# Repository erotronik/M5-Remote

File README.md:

# M5 REMOTE

Please note that this is a modification of the OSSM-M5-Remote project by Ortlof, which is available at [https://github.com/ortlof/OSSM-M5-Remote](https://github.com/ortlof/OSSM-M5-Remote).

Also note that this is an early prototype that is not tested.

This modified project adds RGB Rotary encoders that can light the knobs, and allows the installation of an LED in the push-button.

Furthermore, communication with the board is switched to I2C, using a PWM controller for the LEDs and a port expander for the Rotary encoders. Note that this means that this modification is *not compatible* with the software written for the original OSSM M5 Remote. Currently, there only is a skeleton project [that sketches how to interface with the components on the board in the Firmware folder](./Firmware).

The modified PCB design can be found in the `Hardware/PCB` folder.

The remaining folders in this project are unchanged - please note that the software contained in this repository will not work with the changed hardware.

## Overview of the M5-Remote

The M5 Remote is a remote control platform, e.g. for Sex Toys, or estim devices.

The original project was developed for the OSSM project (https://github.com/KinkyMakers/OSSM-hardware).

This modified version currently does not have direct support for any toys, and requires you to write your own software.

To help with development and design join the KinkyMakers Discord: https://discord.gg/MmpT9xE . Be sure to say hello in the #m5-remote channel. 

# Build the M5 Remote Yourself

## PCB from JLCPCB

The PCB is designed to be made using the JLCPCB assembly service.

To order the PCB, go to [JLCPCP](https://jlcpcb.com) and upload the gerber zip contained in `PCB/jlcpcb`. Leave all settings at default - you can change the PCB colour if you want.

Enable "PCB" assembly, and choose "assemble bottom side" (not selected by default).

In the next step, upload `bom.csv` and `positions.csv`. Verify that the positioning of the components looks corerct before ordering.

## Bill Of Materials for sourcing Electrical Components

BOM is on Octopart for Easy Sourcing: https://octopart.com/bom-tool/pqx0O8QI

## Additional parts needed that are not found on Octopart:

Note - instead of the Kailh switches from pimoroni, any Cherry-compatible switch with LED hole can be used.

| Quantity | Part | Sourcing EU | Price € |
|----------|------|-------------|---------|
| 1x | Switch | https://shop.pimoroni.com/products/kailh-mechanical-switches-pack-of-12?variant=32056315314259 | 7
| 2x | M3x25mm Hex Head Cap Bolt | https://www.amazon.de/Edelstahl-Innensechskant-Bolzenset-Eisenrahmen-Mechanischer-Innensechskantschraube-Mutternset/dp/B07PPFT871/ | 12,97 € |
| 4x | M3x20mm Hex Head Cap Bolt | Comes as part of the set mentioned above | " | 
| 4x | Heat Set inserts M3 | https://www.amazon.de/ruthex-Gewindeeinsatz-St%C3%BCck-Gewindebuchsen-Kunststoffteile/dp/B08BCRZZS3 | 8,99 € |
| 1x | 3,7v 2000mAh Lipo Batterie Size 34,5 mm x 10,6 mm x 56 mm | https://www.amazon.de/EEMB-103454-2AhLithium-Schutzplatine-Isolationsbeschichtung/dp/B08214DJLJ/ | 14,89 € |

--------------------------------------------

| Quantity | Part | Sourcing US | Price $ |
|----------|------|-------------|---------|
| 2x | M3x25mm Hex Head Cap Bolt | https://www.amazon.com/dp/B09NR8X2LV | $17.99 |
| 4x | M3x20mm Hex Head Cap Bolt | Comes as part of the set mentioned above | " | 
| 4x | Heat Set inserts M3 | https://www.amazon.com/ruthex-M3-Threaded-Inserts-RX-M3x5-7/dp/B08BCRZZS3 | $10.99 |
| 1x | 3.7v 2000mAh Lipo Battery Size 34.5 X 56 X 10.6 mm (The wires will need to be reversed in the connector on this one! See Assembly instructions for more info.) | https://www.amazon.com/EEMB-2000mAh-Battery-Rechargeable-Connector/dp/B08214DJLJ/ | $14.99 |

## 3D Printed Parts Needed:

| Quantity | Part | Information |
|----------|------|-------------|
| 1x | Bottom.stl or Bottom_Adafruit_LIPO.stl or Bottom-Magnets.stl| There is a specific version for the wider Adafruit LIPO battery. Print with the base side facing down, 6 walls 20% Infill | 
| 1x | TOP-*-Keycap-Standoff.stl | Top Depends on your Keycap: Cherry or DSA (DSA is wider) | 
| 4x | M5_Remote_Knob_Customizable.scad | If you go for the 3d Printed knobs |

Filament - A good quality PLA works well. While there are no threads it is recommended that your printer is well calibrated.  

# [Assembly instructions](Assembly.md)

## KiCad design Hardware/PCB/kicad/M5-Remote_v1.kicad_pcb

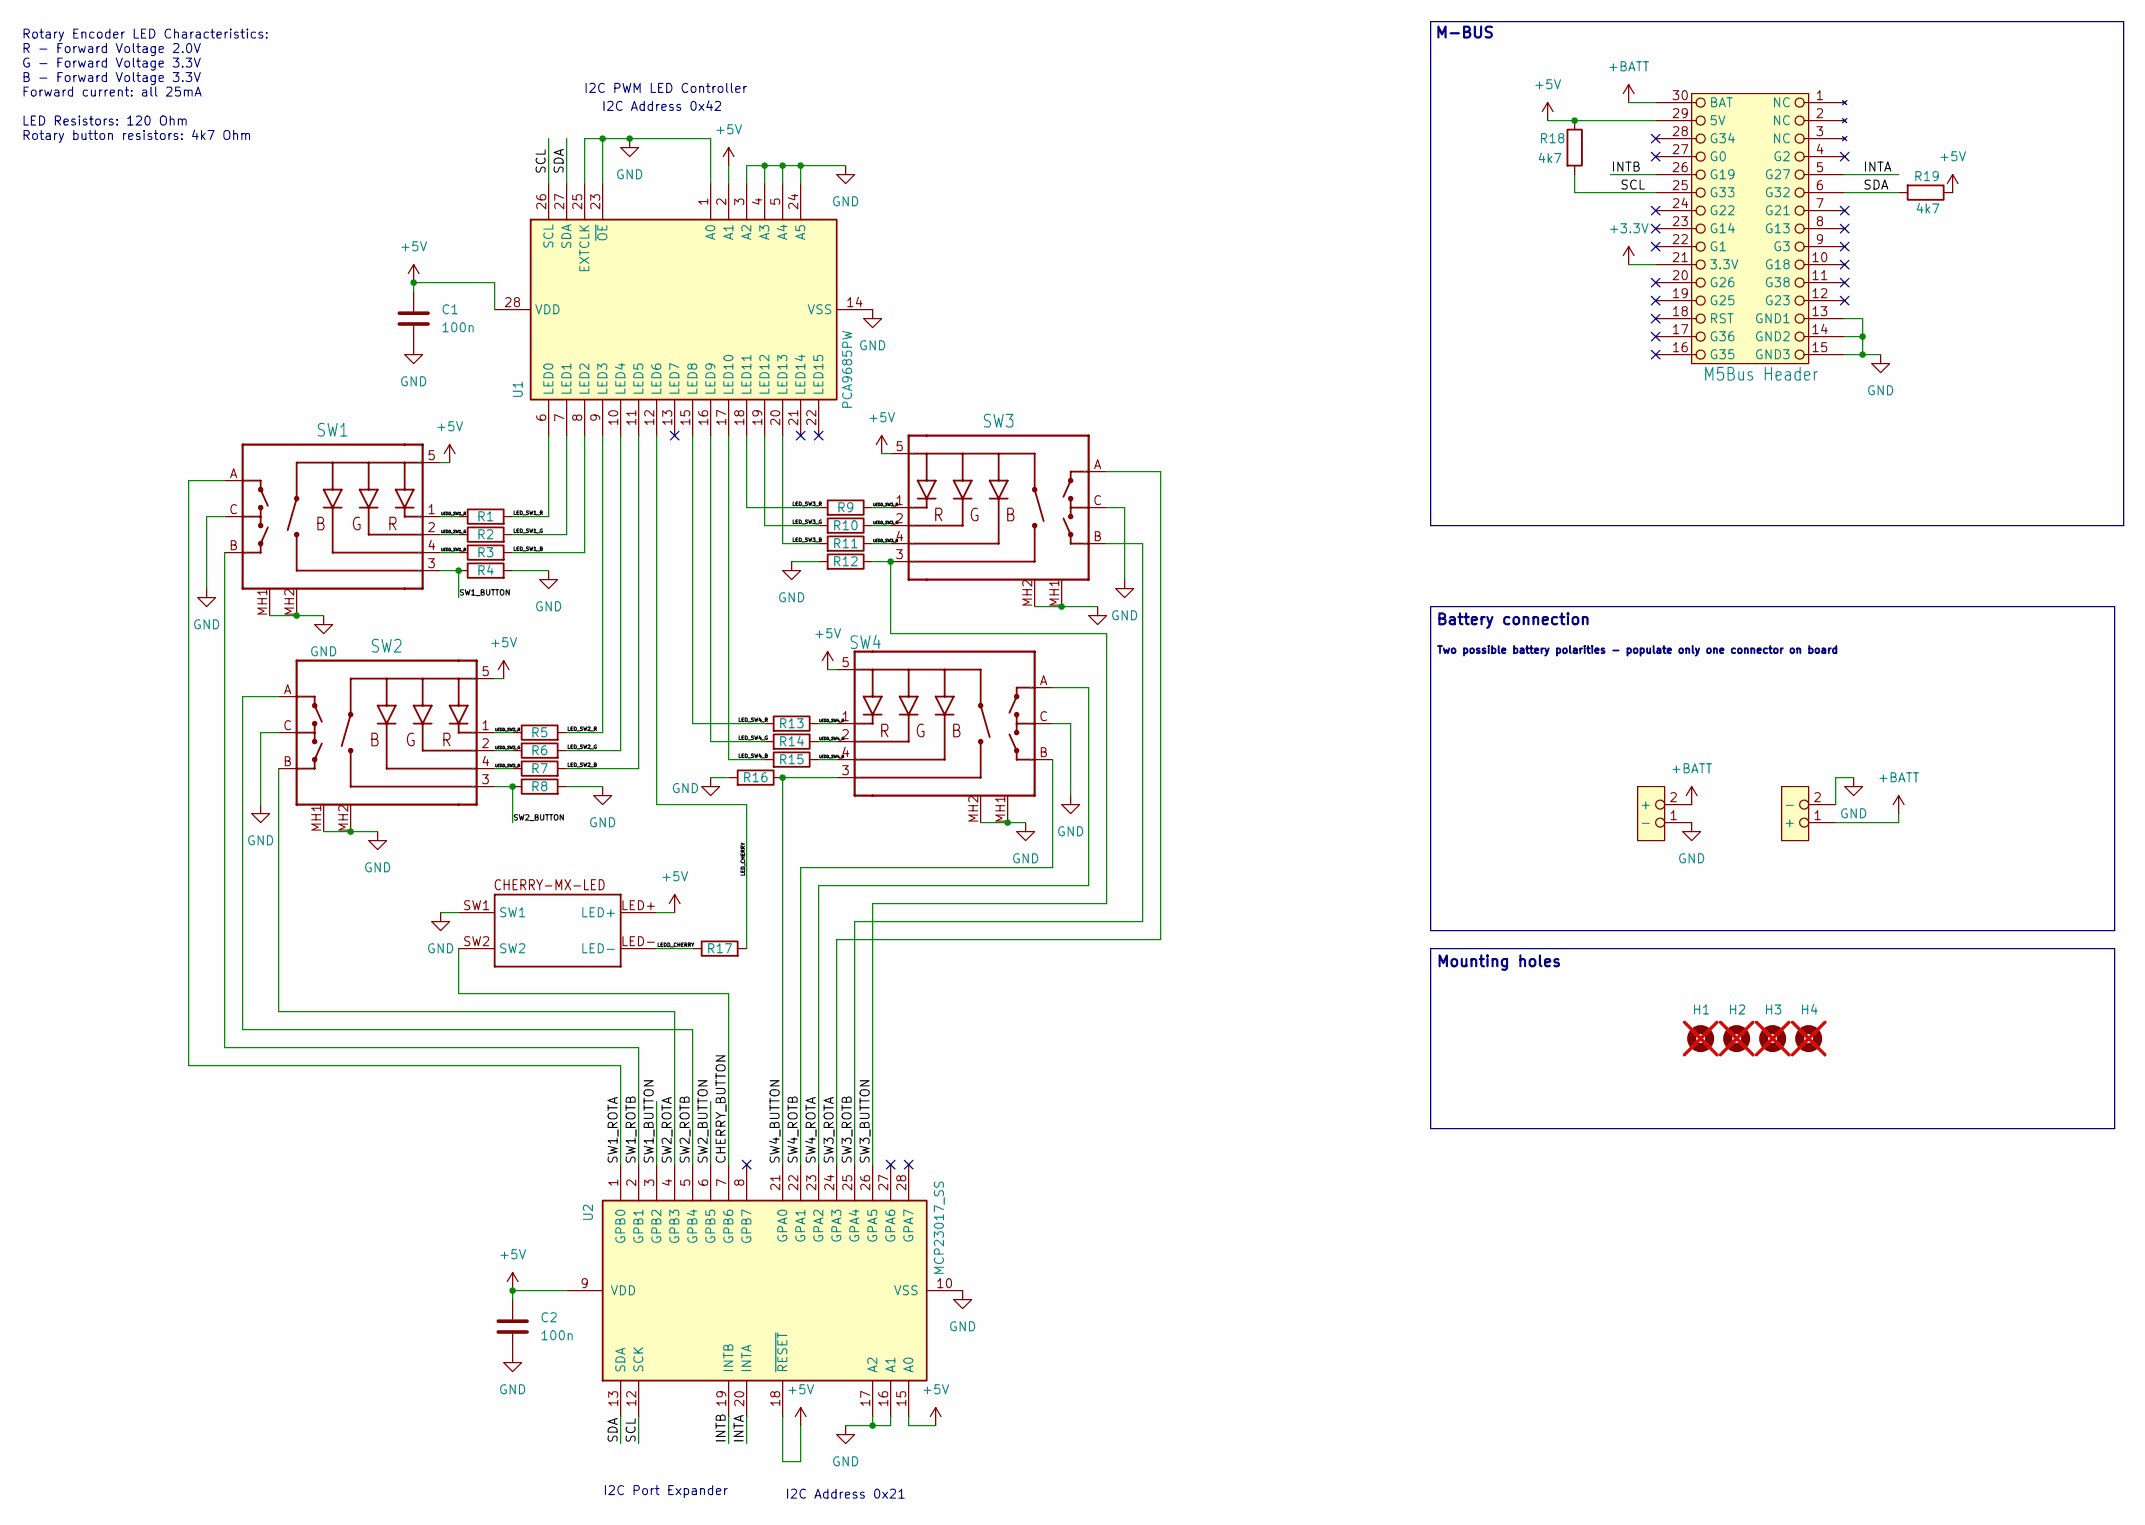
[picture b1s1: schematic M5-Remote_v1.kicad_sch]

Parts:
B1, B2: JST-PH-2MM,180; JST_PH_S2B-PH-K_1x02_P2.00mm_Horizontal
C1, C2: 100n; C_0402_1005Metric; MFR Part Number CL05B104KO5NNNC; LCSC Part # C1525
H1, H2, H3, H4: MountingHole; mounting_hole_3.3mm; not fitted
M5-CORE2: M5Bus Header; M5_CORE2; MFR Part Number 10129381-930001BLF
R1, R2, R3, R5, R6, R7, R9, R10, R11, R13, R14, R15, R17: 120R; R_1206_3216Metric; MFR Part Number 1206W4F1200T5E; LCSC Part # C17909
R4, R8, R12, R16, R18, R19: 4k7; R_1206_3216Metric; MFR Part Number 1206W4F4701T5E; LCSC Part # C17936
SW1, SW2, SW3, SW4: PEL12T4225SS1024; MFR Part Number PEL12T4225SS1024
U1: PCA9685PW; TSSOP-28_4.4x9.7mm_P0.65mm; MFR Part Number PCA9685; LCSC Part # C2678753
U2: MCP23017_SS; SSOP-28_5.3x10.2mm_P0.65mm; MFR Part Number MCP23017-E/SS; LCSC Part # C506653
U3: CHERRY-MX-LED

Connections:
+3.3V: M5-CORE2.21 (3.3V)
+5V: C1.1, C2.1, M5-CORE2.29 (5V), R18.1, R19.1, SW1.5 (+), SW2.5 (+), SW3.5 (+), SW4.5 (+), U1.2 (A1), U1.28 (VDD), U2.9 (VDD), U2.15 (A0), U2.18 (~RESET), U3.LED+
+BATT: B1.2 (+), B2.1 (+), M5-CORE2.30 (BAT)
/CHERRY_BUTTON: U2.7 (GPB6), U3.SW2
/INTA: M5-CORE2.5 (G27), U2.20 (INTA)
/INTB: M5-CORE2.26 (G19), U2.19 (INTB)
/LEDD_CHERRY: R17.1, U3.LED-
/LEDD_SW1_B: R3.1, SW1.4 (-B)
/LEDD_SW1_G: R2.1, SW1.2 (-G)
/LEDD_SW1_R: R1.1, SW1.1 (-R)
/LEDD_SW2_B: R7.1, SW2.4 (-B)
/LEDD_SW2_G: R6.1, SW2.2 (-G)
/LEDD_SW2_R: R5.1, SW2.1 (-R)
/LEDD_SW3_B: R11.1, SW3.4 (-B)
/LEDD_SW3_G: R10.1, SW3.2 (-G)
/LEDD_SW3_R: R9.1, SW3.1 (-R)
/LEDD_SW4_B: R15.1, SW4.4 (-B)
/LEDD_SW4_G: R14.1, SW4.2 (-G)
/LEDD_SW4_R: R13.1, SW4.1 (-R)
/LED_CHERRY: R17.2, U1.12 (LED6)
/LED_SW1_B: R3.2, U1.8 (LED2)
/LED_SW1_G: R2.2, U1.7 (LED1)
/LED_SW1_R: R1.2, U1.6 (LED0)
/LED_SW2_B: R7.2, U1.11 (LED5)
/LED_SW2_G: R6.2, U1.10 (LED4)
/LED_SW2_R: R5.2, U1.9 (LED3)
/LED_SW3_B: R11.2, U1.20 (LED13)
/LED_SW3_G: R10.2, U1.19 (LED12)
/LED_SW3_R: R9.2, U1.18 (LED11)
/LED_SW4_B: R15.2, U1.17 (LED10)
/LED_SW4_G: R14.2, U1.16 (LED9)
/LED_SW4_R: R13.2, U1.15 (LED8)
/SCL: M5-CORE2.25 (G33), R18.2, U1.26 (SCL), U2.12 (SCK)
/SDA: M5-CORE2.6 (G32), R19.2, U1.27 (SDA), U2.13 (SDA)
/SW1_BUTTON: R4.1, SW1.3 (SW), U2.3 (GPB2)
/SW1_ROTA: SW1.A, U2.1 (GPB0)
/SW1_ROTB: SW1.B, U2.2 (GPB1)
/SW2_BUTTON: R8.1, SW2.3 (SW), U2.6 (GPB5)
/SW2_ROTA: SW2.B, U2.4 (GPB3)
/SW2_ROTB: SW2.A, U2.5 (GPB4)
/SW3_BUTTON: R12.1, SW3.3 (SW), U2.26 (GPA5)
/SW3_ROTA: SW3.A, U2.24 (GPA3)
/SW3_ROTB: SW3.B, U2.25 (GPA4)
/SW4_BUTTON: R16.1, SW4.3 (SW), U2.21 (GPA0)
/SW4_ROTA: SW4.A, U2.23 (GPA2)
/SW4_ROTB: SW4.B, U2.22 (GPA1)
GND: B1.1 (-), B2.2 (-), C1.2, C2.2, M5-CORE2.13 (GND1), M5-CORE2.14 (GND2), M5-CORE2.15 (GND3), R4.2, R8.2, R12.2, R16.2, SW1.C, SW1.MH1, SW1.MH2, SW2.C, SW2.MH1, SW2.MH2, SW3.C, SW3.MH1, SW3.MH2, SW4.C, SW4.MH1, SW4.MH2, U1.1 (A0), U1.3 (A2), U1.4 (A3), U1.5 (A4), U1.14 (VSS), U1.23 (~OE), U1.24 (A5), U1.25 (EXTCLK), U2.10 (VSS), U2.16 (A1), U2.17 (A2), U3.SW1

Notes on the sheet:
I2C Address 0x21
I2C Address 0x42
Mounting holes
I2C PWM LED Controller
Battery connection
Rotary Encoder LED Characteristics: R - Forward Voltage 2.0V G - Forward Voltage 3.3V B - Forward Voltage 3.3V Forward current: all 25mA LED Resistors: 120 Ohm Rotary button resistors: 4k7 Ohm
Two possible battery polarities - populate only one connector on board
M-BUS
I2C Port Expander

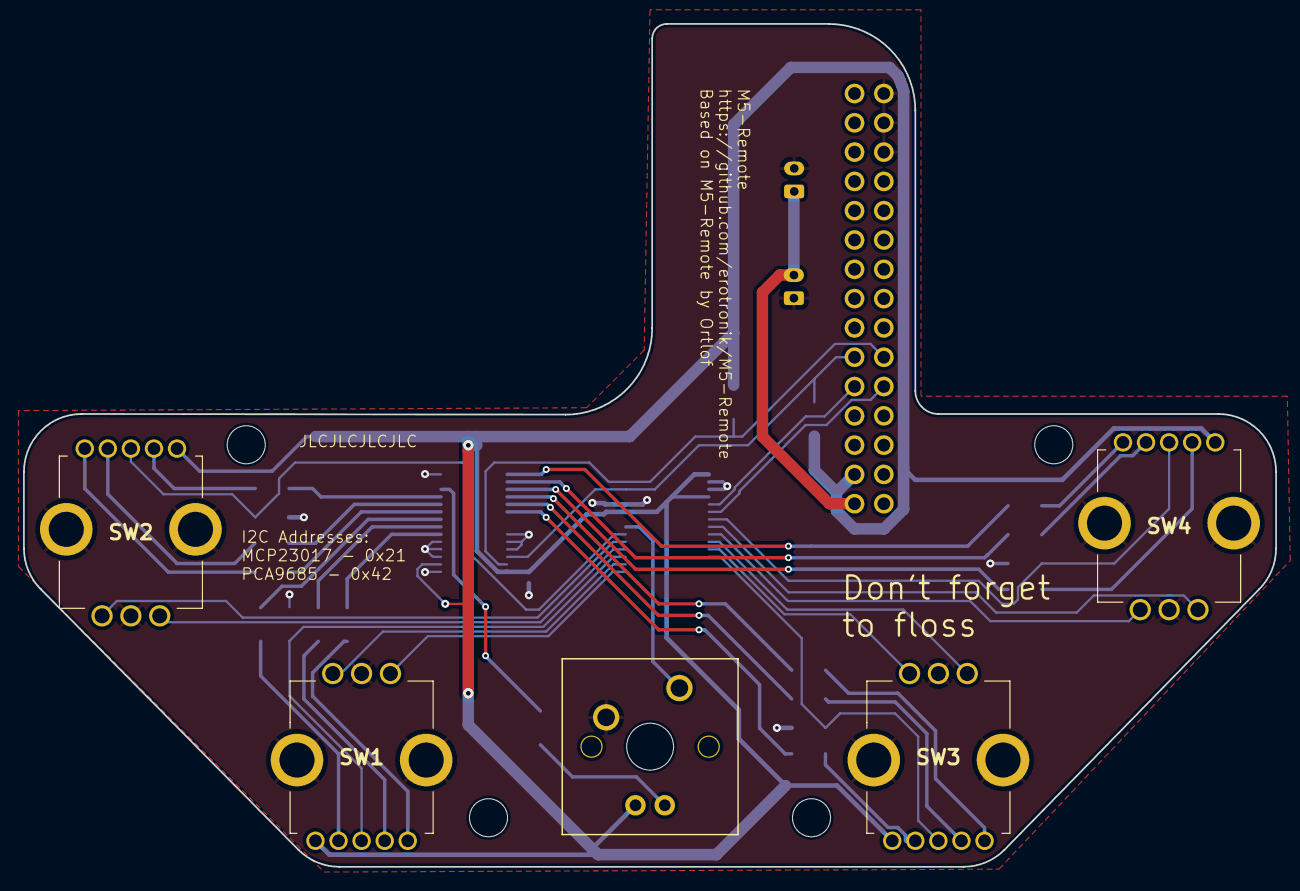
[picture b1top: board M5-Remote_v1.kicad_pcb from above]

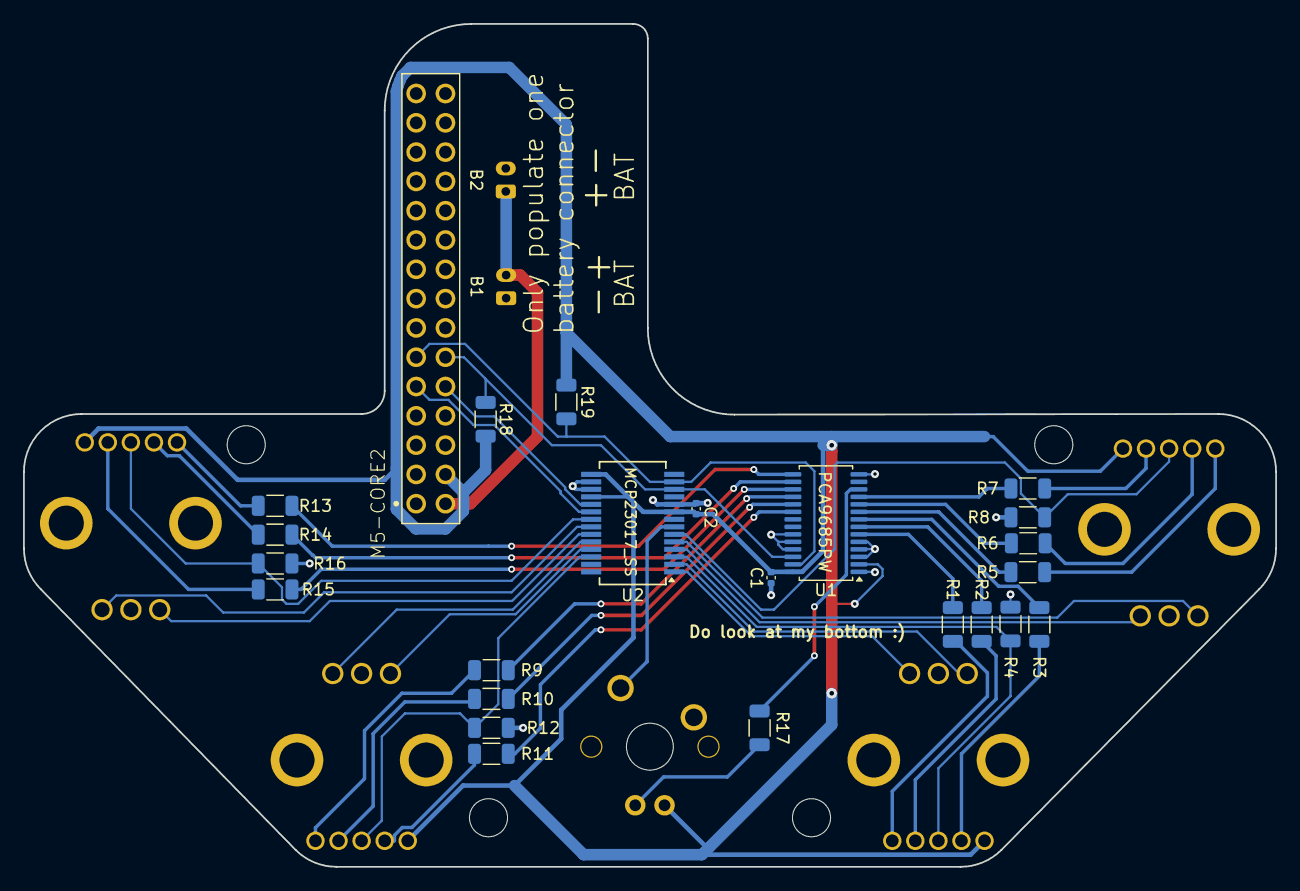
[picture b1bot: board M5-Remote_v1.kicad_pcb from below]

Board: 2 copper layers, 108.5 x 73.1 mm, 35 parts (26 on the bottom side), 46 nets.

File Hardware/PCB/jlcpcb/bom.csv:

Designator,Footprint,Quantity,Value,LCSC Part #
"C1, C2",0402,2,100n,C1525
"R1, R10, R11, R13, R14, R15, R17, R2, R3, R5, R6, R7, R9",1206,13,120R,C17909
"R12, R16, R18, R19, R4, R8",1206,6,4k7,C17936
U1,TSSOP-28_4.4x9.7mm_P0.65mm,1,PCA9685PW,C2678753
U2,SSOP-28_5.3x10.2mm_P0.65mm,1,MCP23017_SS,C506653

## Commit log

2024-02-12 Add current version and eagle exports
2024-02-12 kicad import
2024-02-16 Update schematic, remove traces
2024-03-21 Cleaner schematic
2024-03-22 Starting routing
2024-03-22 Everything connected
2024-03-26 PCB updates
2024-03-26 Big rename
2024-03-27 Final touches for first PCB version
2024-04-22 Tiny fix
2024-04-22 Update readmes
2024-04-22 Remove source
    Does not work with this version of the hardware.
2024-04-23 Add skeleton firmware
2024-04-23 Add some sample code for the CoreS3 and the new hardware
2024-04-23 Don't enable the pullups on the switches for rotary encoders, they are already pull down
2024-04-23 A little cleanup ready to add some encoder handling
2024-04-23 Cleanup. Tell MCP to just mirror the interrupt to both pins so we can ignore one anyway
2024-04-23 Test rotary
2024-04-23 Working with a thread
2024-04-23 Clean up the messy test code
2024-04-23 No need to invert output from switches, remember to clear interrupts
2024-04-26 Add a title and make the scrolling bit smaller
2024-04-26 Debounce time was causing some quick presses to be ignored, reduce it. Fix silly logic to something more simplest
2024-04-26 New remote pic
2024-05-01 Just move the IO m5 stuff to a header file for now to make it easier to include it in other projects, can be made into a library etc later
